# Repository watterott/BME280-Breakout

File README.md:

# BME280-Breakout
Breakout with BME280 Digital Environmental Sensor from Bosch Sensortec.

* [Bosch BME280](https://www.bosch-sensortec.com/en/bst/products/all_products/bme280) Integrated Environmental Sensor (Humidity, Pressure and Temperature)
* Temperature Sensor -40...85°C
* Pressure Sensor 300...1100hPa (+9000...-500m above/below sea level)
* Humidity Sensor 0...100%
* On-board 3.3V voltage regulator
* SPI Interface (up to 10MHz)
* TWI/I2C Interface (address 0x76 when SDO=0 or 0x77 when SDO=1, CS=1 for I2C)
* 3.3V - 5V Power Supply and Logic Level
* Open-Source and released under the [Creative Commons Attribution Share-Alike License](https://creativecommons.org/licenses/by-sa/4.0/).
* **[Documentation on learn.watterott.com](https://learn.watterott.com)**

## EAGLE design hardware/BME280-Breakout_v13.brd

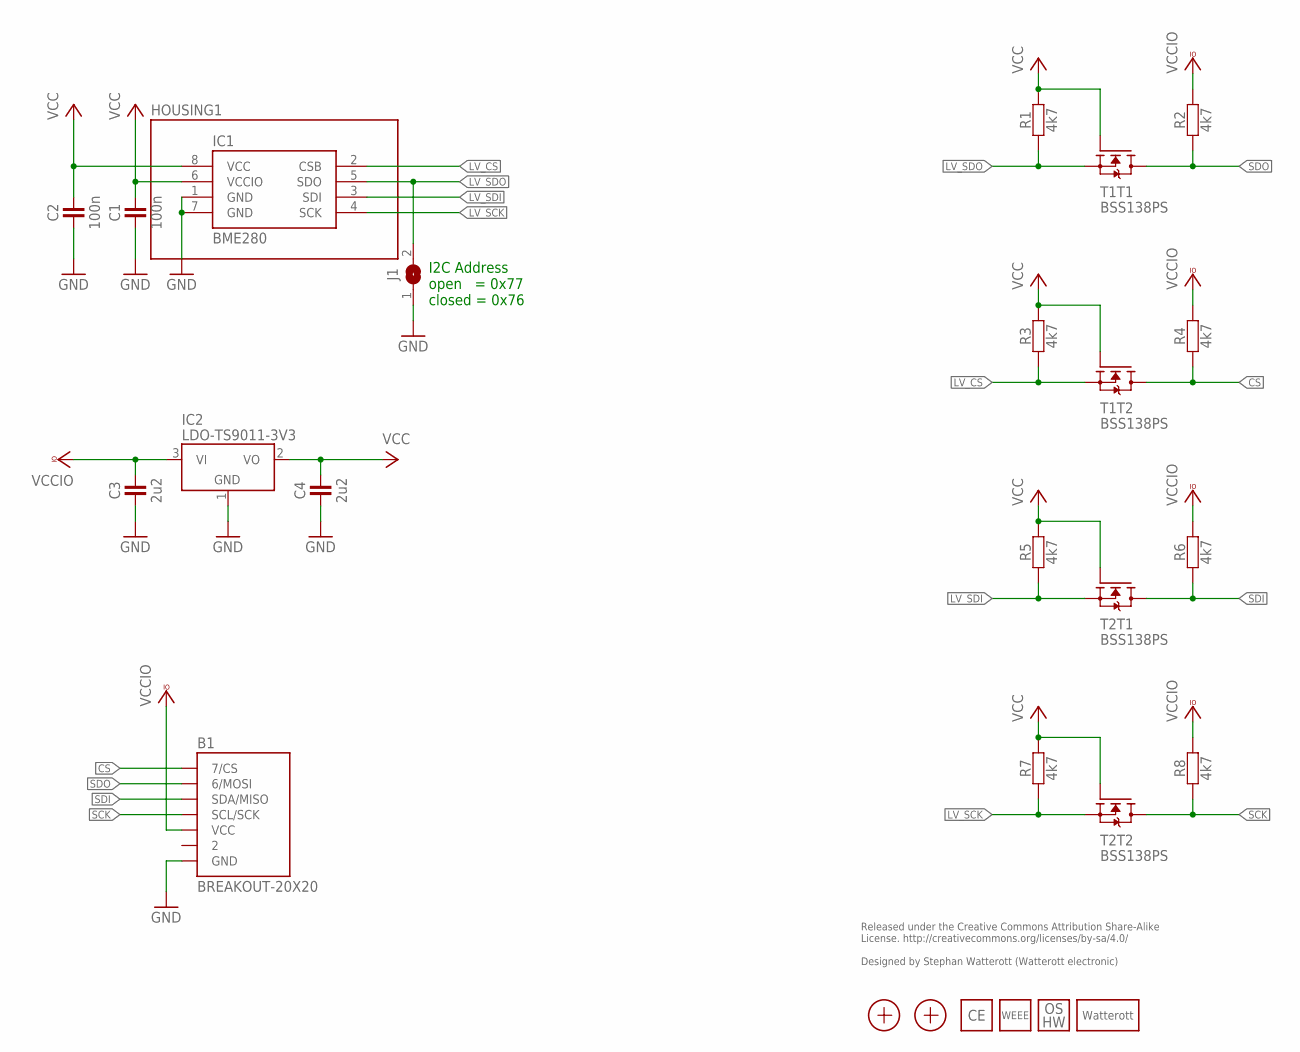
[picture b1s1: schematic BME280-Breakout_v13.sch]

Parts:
B1: BREAKOUT-20X20
C1, C2: 100n; C0402
C3, C4: 2u2; C0402
HOUSING1: SF2
IC1: BME280
IC2: LDO-TS9011-3V3; SOT23
J1: JUMPER2-0603
LOGO3: LOGO_CE-2; CE_2MM
LOGO4: LOGO_WEEE-4; WEEE_4MM
LOGO5: LOGO_SPARK-2; SPARK_2MM
LOGO6: LOGO_OSHW-2; OSHW_2MM
R1, R2, R3, R4, R5, R6, R7, R8: 4k7; C0402
T1, T2: BSS138PS; SOT363
X1, X2: PASSER-07; PASSER_07MM

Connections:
CS: B1.CS (7/CS), R4.1, T1.3 (D)
GND: B1.GND, C1.1, C2.1, C3.1, C4.1, IC1.1 (GND), IC1.7 (GND), IC2.1 (GND), J1.1
LV_CS: IC1.2 (CSB), R3.1, T1.4 (S)
LV_SCK: IC1.4 (SCK), R7.1, T2.4 (S)
LV_SDI: IC1.3 (SDI), R5.1, T2.1 (S)
LV_SDO: IC1.5 (SDO), J1.2, R1.1, T1.1 (S)
SCK: B1.SCL/SCK, R8.1, T2.3 (D)
SDI: B1.SDA/MISO, R6.1, T2.6 (D)
SDO: B1.MOSI (6/MOSI), R2.1, T1.6 (D)
VCC: C1.2, C2.2, C4.2, IC1.6 (VCCIO), IC1.8 (VCC), IC2.2 (VO), R1.2, R3.2, R5.2, R7.2, T1.2 (G), T1.5 (G), T2.2 (G), T2.5 (G)
VCCIO: B1.VCC, C3.2, IC2.3 (VI), R2.2, R4.2, R6.2, R8.2

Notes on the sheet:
I2C Address open = 0x77 closed = 0x76
Released under the Creative Commons Attribution Share-Alike License. http://creativecommons.org/licenses/by-sa/4.0/ Designed by Stephan Watterott (Watterott electronic)

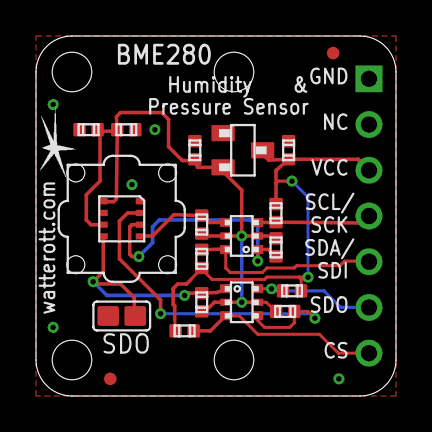
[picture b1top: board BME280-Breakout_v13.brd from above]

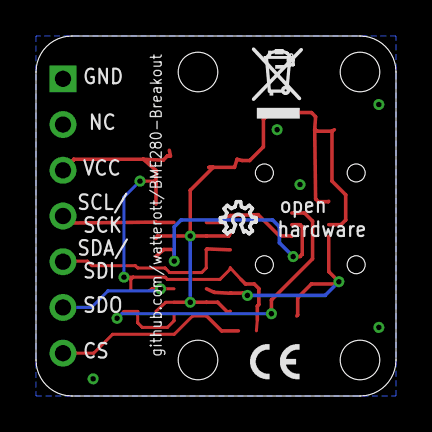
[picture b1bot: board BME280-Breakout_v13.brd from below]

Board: 2 copper layers, 20.0 x 20.0 mm, 25 parts (3 on the bottom side), 11 nets.

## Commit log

2018-05-01 added rev 1.1
2018-09-27 updated schematics
2018-09-27 added rev 1.2
2019-11-03 added rev 1.3
